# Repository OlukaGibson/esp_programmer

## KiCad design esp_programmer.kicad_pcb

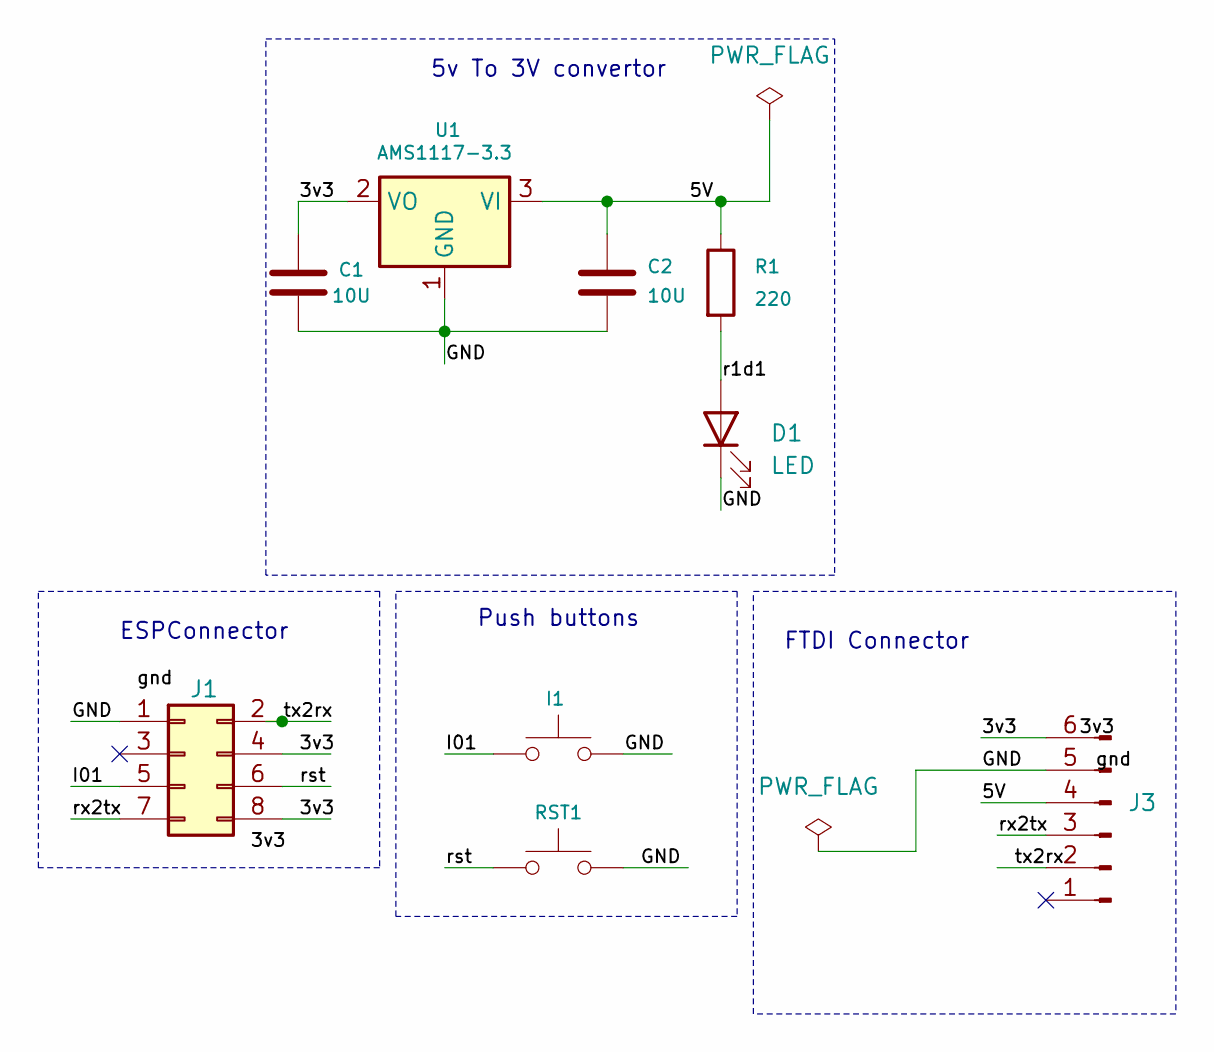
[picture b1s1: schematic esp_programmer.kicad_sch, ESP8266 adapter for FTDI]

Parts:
C1, C2: 10U; C_0201_0603Metric
D1: LED; LED_0201_0603Metric
I1: I01; SW_PUSH_1P1T_6x3.5mm_H4.3_APEM_MJTP1243
J1: PinSocket_2x04_P2.54mm_Vertical
J3: Conn_01x06_Pin; PinHeader_1x06_P2.54mm_Vertical
R1: 220; R_0201_0603Metric_Pad0.64x0.40mm_HandSolder
RST1: RST; SW_PUSH_1P1T_6x3.5mm_H4.3_APEM_MJTP1243
U1: AMS1117-3.3; SOT-223-3_TabPin2

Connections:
/3v3: C1.1, J1.4, J1.8, J3.6, U1.2 (VO)
/5V: C2.1, J3.4, R1.1, U1.3 (VI)
/GND: C1.2, C2.2, D1.1 (K), I1.2, J1.1, J3.5, RST1.2, U1.1 (GND)
/I01: I1.1, J1.5
/r1d1: D1.2 (A), R1.2
/rst: J1.6, RST1.1
/rx2tx: J1.7, J3.3
/tx2rx: J1.2, J3.2

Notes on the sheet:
5v To 3V convertor
FTDI Connector
Push buttons
ESPConnector

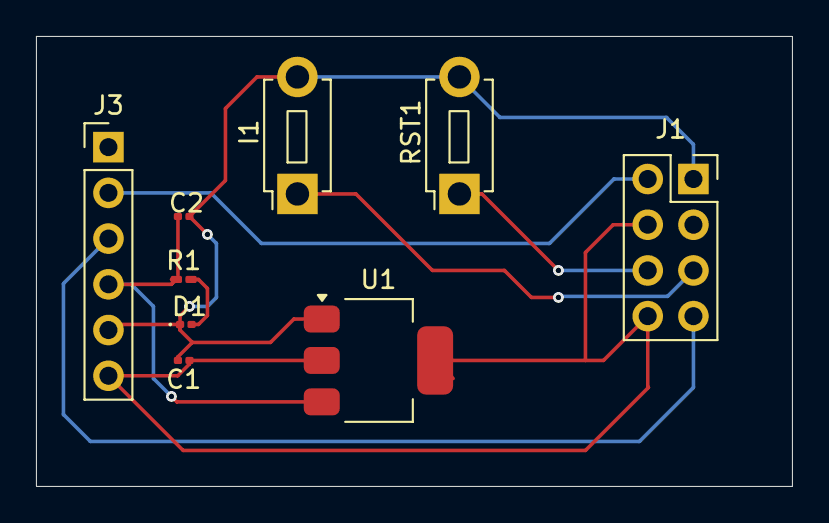
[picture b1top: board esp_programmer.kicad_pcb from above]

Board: 2 copper layers, 42.0 x 25.0 mm, 9 parts (0 on the bottom side), 8 nets.

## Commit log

2024-11-18 New push
